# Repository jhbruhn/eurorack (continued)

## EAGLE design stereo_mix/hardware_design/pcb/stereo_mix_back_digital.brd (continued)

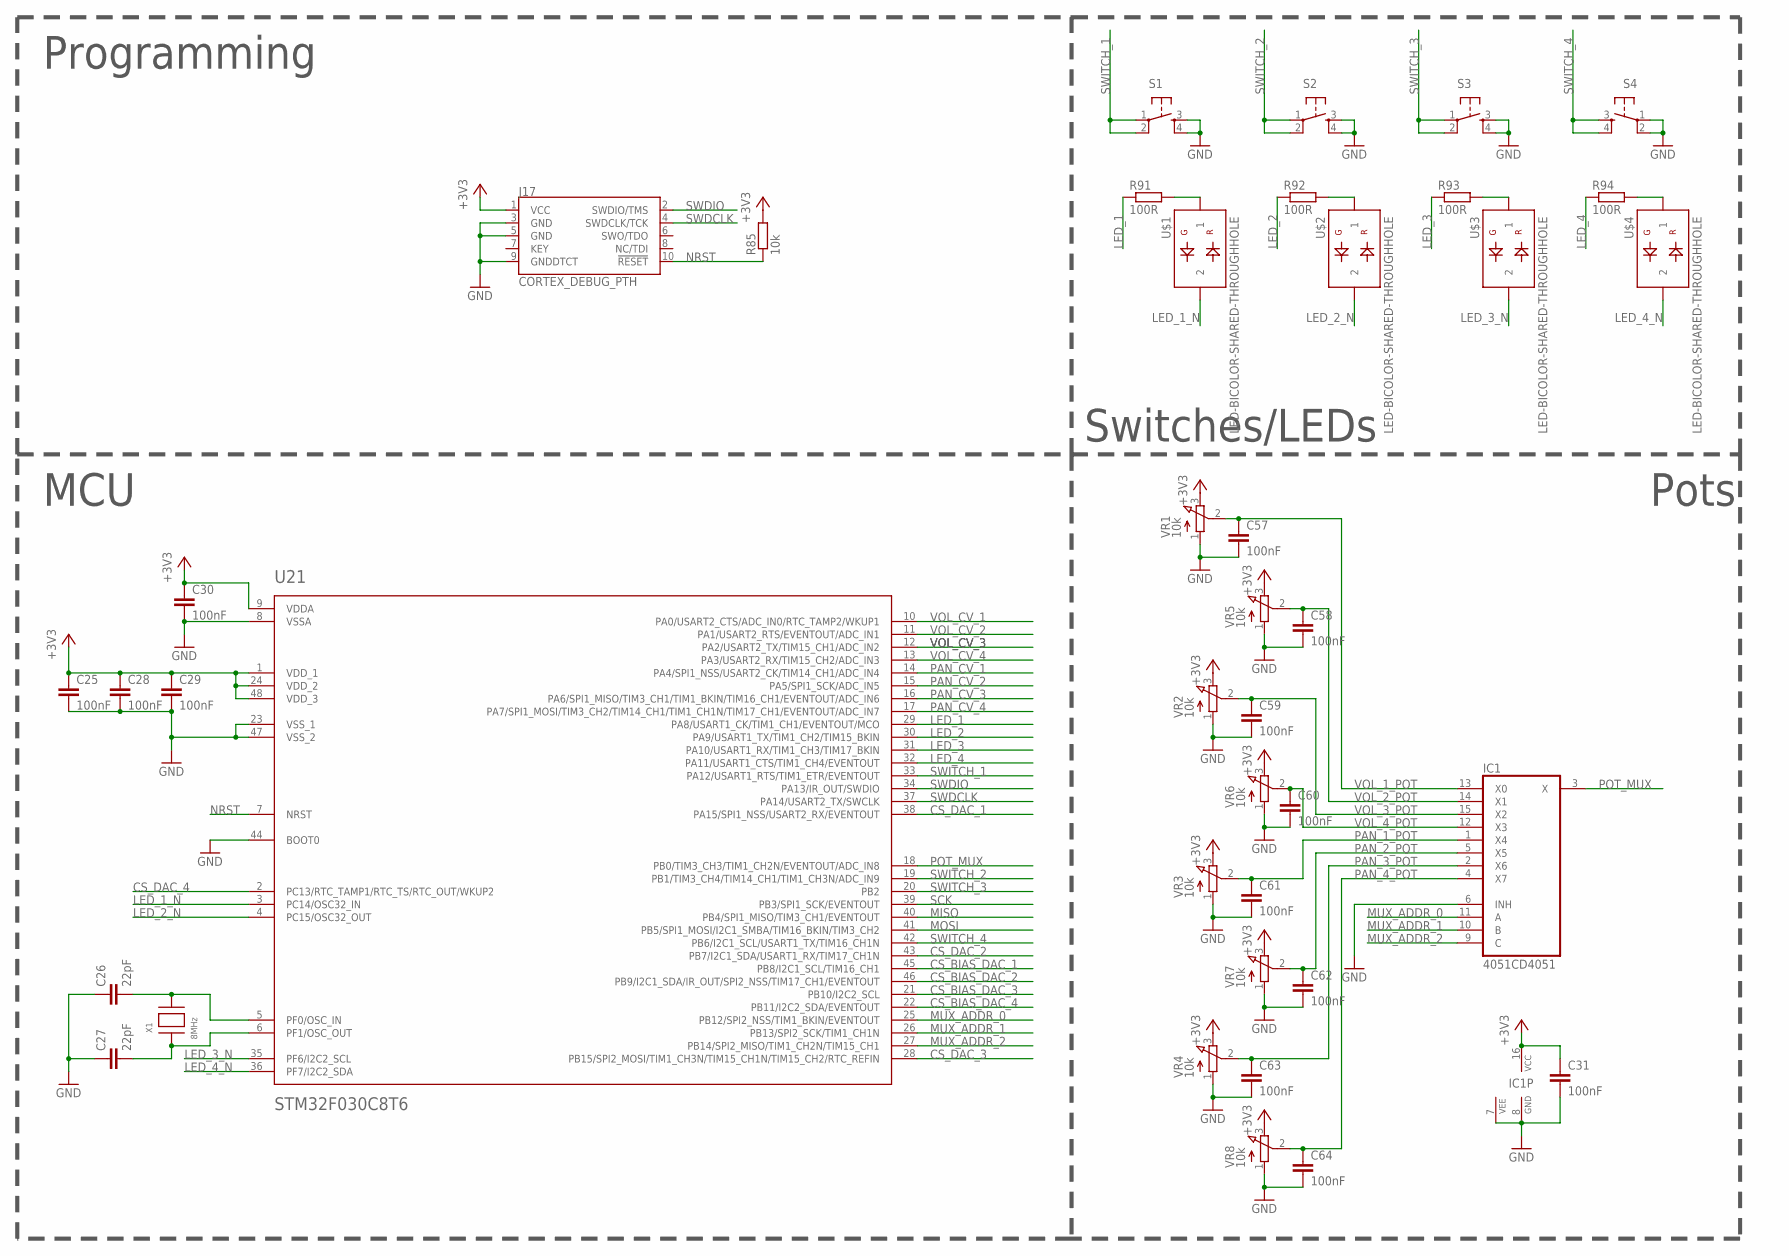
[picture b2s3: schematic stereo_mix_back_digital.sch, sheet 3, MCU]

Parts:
C25, C28, C29, C30, C31, C57, C58, C59, C60, C61, C62, C63, C64: 100nF; C0402
C26, C27: 22pF; C0402
IC1: 4051CD4051; SOIC16N
J17: CORTEX_DEBUG_PTH; 2X5-PTH-1.27MM
R85: 10k; R0402
R91, R92, R93, R94: 100R; R0402
S1, S2, S3, S4: TAC_SWITCHPTH; TACTILE-PTH
U21: STM32F030C8T6; LQFP48
U$1, U$2, U$3, U$4: LED-BICOLOR-SHARED-THROUGHHOLE; LED3MM
VR1, VR2, VR3, VR4, VR5, VR6, VR7, VR8: 10k; 9MM_SNAP-IN_POT
X1: 8MHz; NX5032

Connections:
+3V3: C25.1, C28.1, C29.1, C30.1, C31.1, IC1.16 (VCC), J17.1 (VCC), R85.2, U21.1 (VDD_1), U21.9 (VDDA), U21.24 (VDD_2), U21.48 (VDD_3), VR1.3 (E), VR2.3 (E), VR3.3 (E), VR4.3 (E), VR5.3 (E), VR6.3 (E), VR7.3 (E), VR8.3 (E); also elsewhere on the board
CS_BIAS_DAC_1: U21.45 (PB8/I2C1_SCL/TIM16_CH1); also elsewhere on the board
CS_BIAS_DAC_2: U21.46 (PB9/I2C1_SDA/IR_OUT/SPI2_NSS/TIM17_CH1/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); also elsewhere on the board
CS_BIAS_DAC_3: U21.21 (PB10/I2C2_SCL); also elsewhere on the board
CS_BIAS_DAC_4: U21.22 (PB11/I2C2_SDA/EVENTOUT); also elsewhere on the board
CS_DAC_1: U21.38 (PA15/SPI1_NSS/USART2_RX/EVENTOUT); also elsewhere on the board
CS_DAC_2: U21.43 (PB7/I2C1_SDA/USART1_RX/TIM17_CH1N); also elsewhere on the board
CS_DAC_3: U21.28 (PB15/SPI2_MOSI/TIM1_CH3N/TIM15_CH1N/TIM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); also elsewhere on the board
CS_DAC_4: U21.2 (PC13/RTC_TAMP1/RTC_TS/RTC_OUT/WKUP2); also elsewhere on the board
GND: C25.2, C26.1, C27.1, C28.2, C29.2, C30.2, C31.2, C57.2, C58.2, C59.2, C60.2, C61.2, C62.2, C63.2, C64.2, IC1.6 (INH), IC1.7 (VEE), IC1.8 (GND), J17.3 (GND), J17.5 (GND), J17.9 (GNDDTCT), S1.3, S1.4, S2.3, S2.4, S3.3, S3.4, S4.1, S4.2, U21.8 (VSSA), U21.23 (VSS_1), U21.44 (BOOT0), U21.47 (VSS_2), VR1.1 (A), VR2.1 (A), VR3.1 (A), VR4.1 (A), VR5.1 (A), VR6.1 (A), VR7.1 (A), VR8.1 (A); also elsewhere on the board
LED_1: R91.1, U21.29 (PA8/USART1_CK/TIM1_CH1/EVENTOUT/MCO)
LED_1_N: U21.3 (PC14/OSC32_IN), U$1.2
LED_2: R92.1, U21.30 (PA9/USART1_TX/TIM1_CH2/TIM15_BKIN)
LED_2_N: U21.4 (PC15/OSC32_OUT), U$2.2
LED_3: R93.1, U21.31 (PA10/USART1_RX/TIM1_CH3/TIM17_BKIN)
LED_3_N: U21.35 (PF6/I2C2_SCL), U$3.2
LED_4: R94.1, U21.32 (PA11/USART1_CTS/TIM1_CH4/EVENTOUT)
LED_4_N: U21.36 (PF7/I2C2_SDA), U$4.2
MISO: U21.40 (PB4/SPI1_MISO/TIM3_CH1/EVENTOUT)
MOSI: U21.41 (PB5/SPI1_MOSI/I2C1_SMBA/TIM16_BKIN/TIM3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); also elsewhere on the board
MUX_ADDR_0: IC1.11 (A), U21.25 (PB12/SPI2_NSS/TIM1_BKIN/EVENTOUT)
MUX_ADDR_1: IC1.10 (B), U21.26 (PB13/SPI2_SCK/TIM1_CH1N)
MUX_ADDR_2: IC1.9 (C), U21.27 (PB14/SPI2_MISO/TIM1_CH2N/TIM15_CH1)
unnamed: R91.2, U$1.1
unnamed: R92.2, U$2.1
unnamed: R93.2, U$3.1
unnamed: R94.2, U$4.1
unnamed: C27.2, U21.6 (PF1/OSC_OUT), X1.P$1
unnamed: C26.2, U21.5 (PF0/OSC_IN), X1.P$2
NRST: J17.10 (!RESET), R85.1, U21.7 (NRST)
PAN_1_POT: C61.1, IC1.1 (X4), VR3.2 (S)
PAN_2_POT: C62.1, IC1.5 (X5), VR7.2 (S)
PAN_3_POT: C63.1, IC1.2 (X6), VR4.2 (S)
PAN_4_POT: C64.1, IC1.4 (X7), VR8.2 (S)
PAN_CV_1: U21.14 (PA4/SPI1_NSS/USART2_CK/TIM14_CH1/ADC_IN4); also elsewhere on the board
PAN_CV_2: U21.15 (PA5/SPI1_SCK/ADC_IN5); also elsewhere on the board
PAN_CV_3: U21.16 (PA6/SPI1_MISO/TIM3_CH1/TIM1_BKIN/TIM16_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); also elsewhere on the board
PAN_CV_4: U21.17 (PA7/SPI1_MOSI/TIM3_CH2/TIM14_CH1/TIM1_C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); also elsewhere on the board
POT_MUX: IC1.3 (X), U21.18 (PB0/TIM3_CH3/TIM1_CH2N/EVENTOUT/ADC_IN8)
SCK: U21.39 (PB3/SPI1_SCK/EVENTOUT); also elsewhere on the board
SWDCLK: J17.4 (SWDCLK/TCK), U21.37 (PA14/USART2_TX/SWCLK)
SWDIO: J17.2 (SWDIO/TMS), U21.34 (PA13/IR_OUT/SWDIO)
SWITCH_1: S1.1, S1.2, U21.33 (PA12/USART1_RTS/TIM1_ETR/EVENTOUT)
SWITCH_2: S2.1, S2.2, U21.19 (PB1/TIM3_CH4/TIM14_CH1/TIM1_CH3N/ADC_IN9)
SWITCH_3: S3.1, S3.2, U21.20 (PB2)
SWITCH_4: S4.3, S4.4, U21.42 (PB6/I2C1_SCL/USART1_TX/TIM16_CH1N)
VOL_1_POT: C57.1, IC1.13 (X0), VR1.2 (S)
VOL_2_POT: C58.1, IC1.14 (X1), VR5.2 (S)
VOL_3_POT: C59.1, IC1.15 (X2), VR2.2 (S)
VOL_4_POT: C60.1, IC1.12 (X3), VR6.2 (S)
VOL_CV_1: U21.10 (PA0/USART2_CTS/ADC_IN0/RTC_TAMP2/WKUP1); also elsewhere on the board
VOL_CV_2: U21.11 (PA1/USART2_RTS/EVENTOUT/ADC_IN1); also elsewhere on the board
VOL_CV_3: U21.12 (PA2/USART2_TX/TIM15_CH1/ADC_IN2); also elsewhere on the board
VOL_CV_4: U21.13 (PA3/USART2_RX/TIM15_CH2/ADC_IN3); also elsewhere on the board

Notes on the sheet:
MCU
Pots
Switches/LEDs
Programming

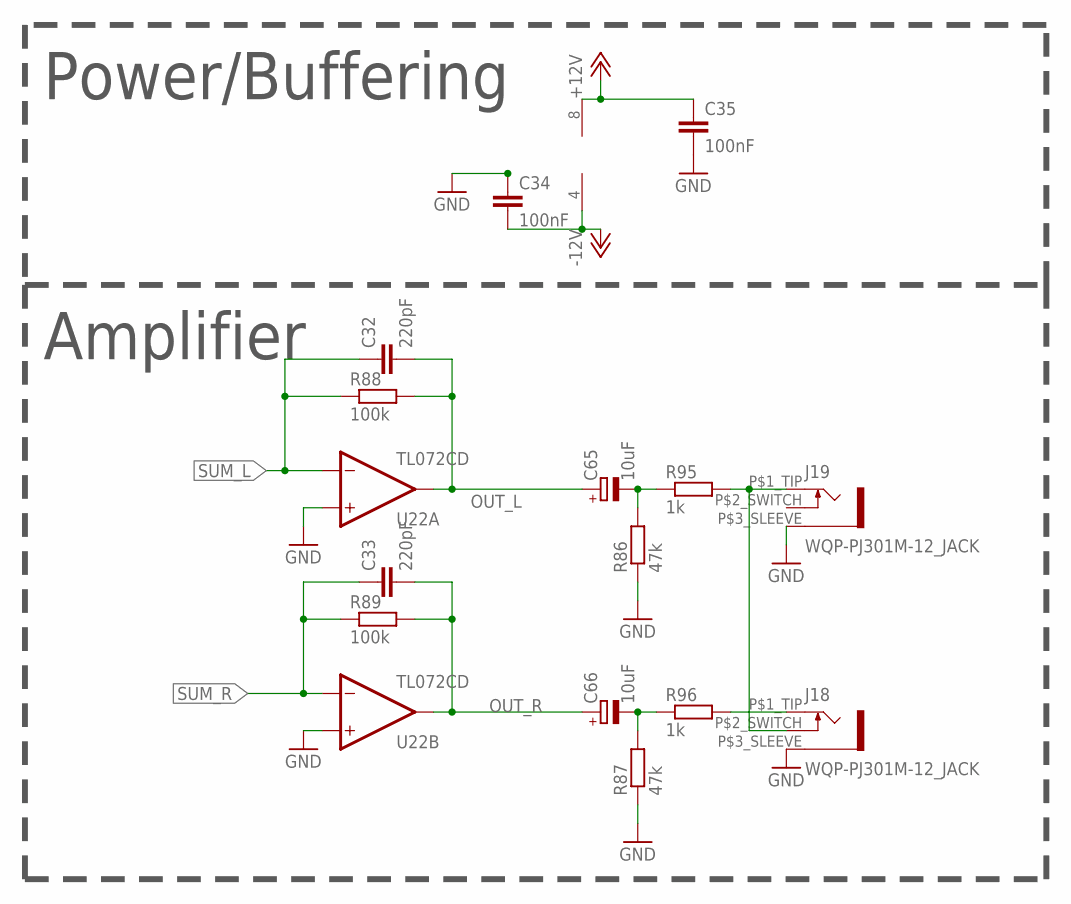
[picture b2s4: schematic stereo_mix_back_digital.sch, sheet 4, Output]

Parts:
C32, C33: 220pF; C0402
C34, C35: 100nF; C0402
C65, C66: 10uF; CASE-A_3216
J18, J19: WQP-PJ301M-12_JACK
R86, R87: 47k; R0402
R88, R89: 100k; R0402
R95, R96: 1k; R0402
U22: TL072CD; SOIC8

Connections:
+12V: C35.1, U22.8 (V+); also elsewhere on the board
-12V: C34.2, U22.4 (V-); also elsewhere on the board
GND: C34.1, C35.2, J18.P$3_SLEEVE (1), J19.P$3_SLEEVE (1), R86.1, R87.1, U22.3 (+IN), U22.5 (+IN); also elsewhere on the board
unnamed: J18.P$2_SWITCH (3), J19.P$1_TIP (2), R95.2
unnamed: C65.-, R86.2, R95.1
unnamed: J18.P$1_TIP (2), R96.2
unnamed: C66.-, R87.2, R96.1
OUT_L: C32.2, C65.+, R88.2, U22.1 (OUT)
OUT_R: C33.2, C66.+, R89.2, U22.7 (OUT)
SUM_L: C32.1, R88.1, U22.2 (-IN); also elsewhere on the board
SUM_R: C33.1, R89.1, U22.6 (-IN); also elsewhere on the board

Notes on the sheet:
Power/Buffering
Amplifier

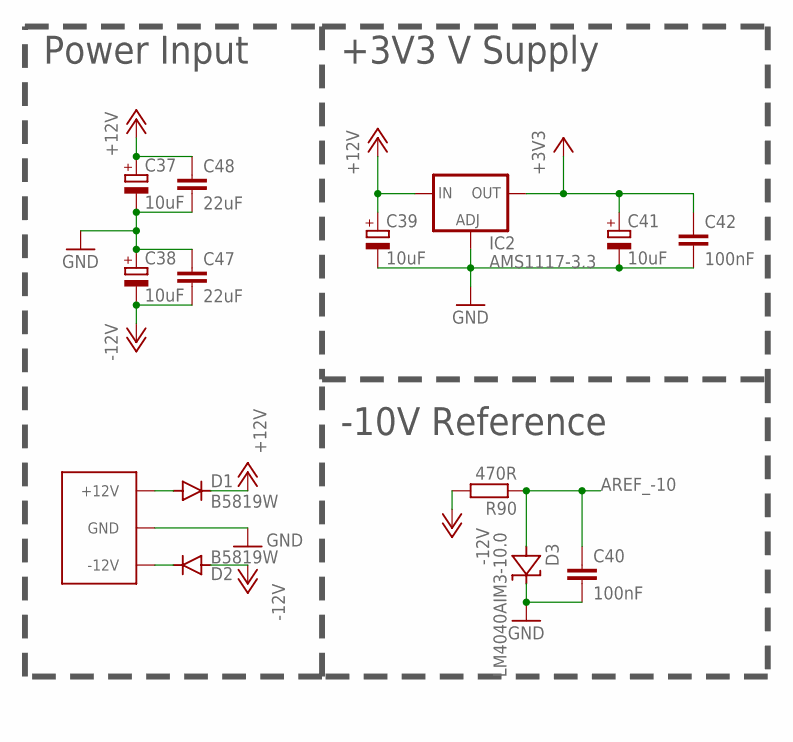
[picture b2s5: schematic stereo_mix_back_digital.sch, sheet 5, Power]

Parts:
C36: EURO_POWER_LOCKFAT-LOCK; EURO_PWR_HEADER_LOCK
C37, C38, C39, C41: 10uF; CASE-A_3216
C40, C42: 100nF; C0402
C47, C48: 22uF; C0805
D1, D2: B5819W; SOD123
D3: LM4040AIM3-10.0; SOT23
IC2: AMS1117-3.3; SOT223
R90: 470R; R0402

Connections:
+3V3: C41.+, C42.1, IC2.4 (OUT); also elsewhere on the board
+12V: C37.+, C39.+, C48.1, D1.C, IC2.3 (IN); also elsewhere on the board
-12V: C38.-, C47.2, D2.A, R90.2; also elsewhere on the board
AREF_-10: C40.1, D3.2 (A), R90.1; also elsewhere on the board
GND: C36.GND1 (GND), C36.GND2 (GND), C36.GND3 (GND), C36.GND4 (GND), C36.GND5 (GND), C36.GND6 (GND), C37.-, C38.+, C39.-, C40.2, C41.-, C42.2, C47.1, C48.2, D3.1 (C), IC2.1 (ADJ); also elsewhere on the board
unnamed: C36.POS1 (+12V), C36.POS2 (+12V), D1.A
unnamed: C36.NEG1 (-12V), C36.NEG2 (-12V), D2.C

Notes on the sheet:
Power Input
+3V3 V Supply
-10V Reference

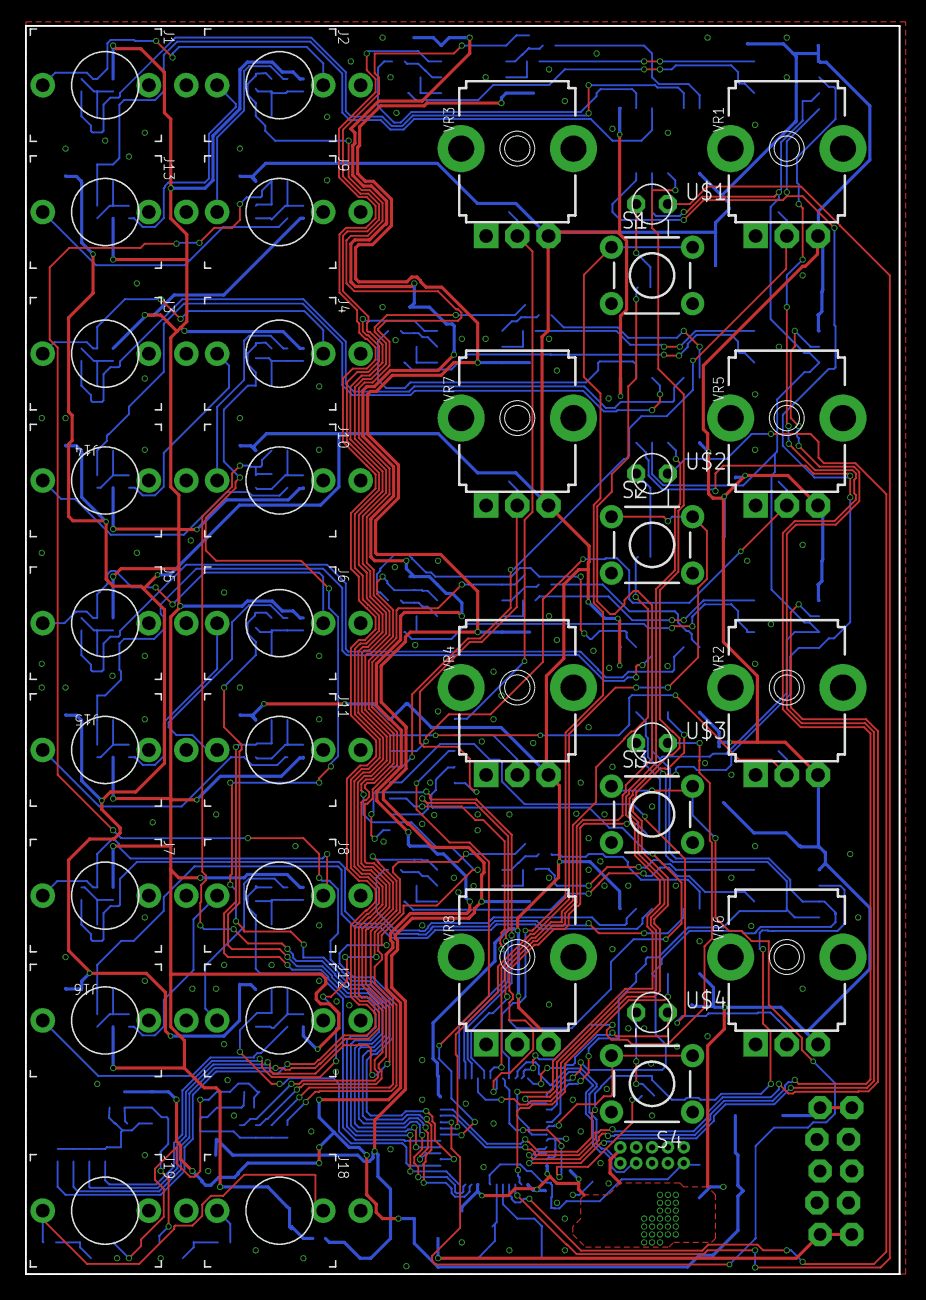
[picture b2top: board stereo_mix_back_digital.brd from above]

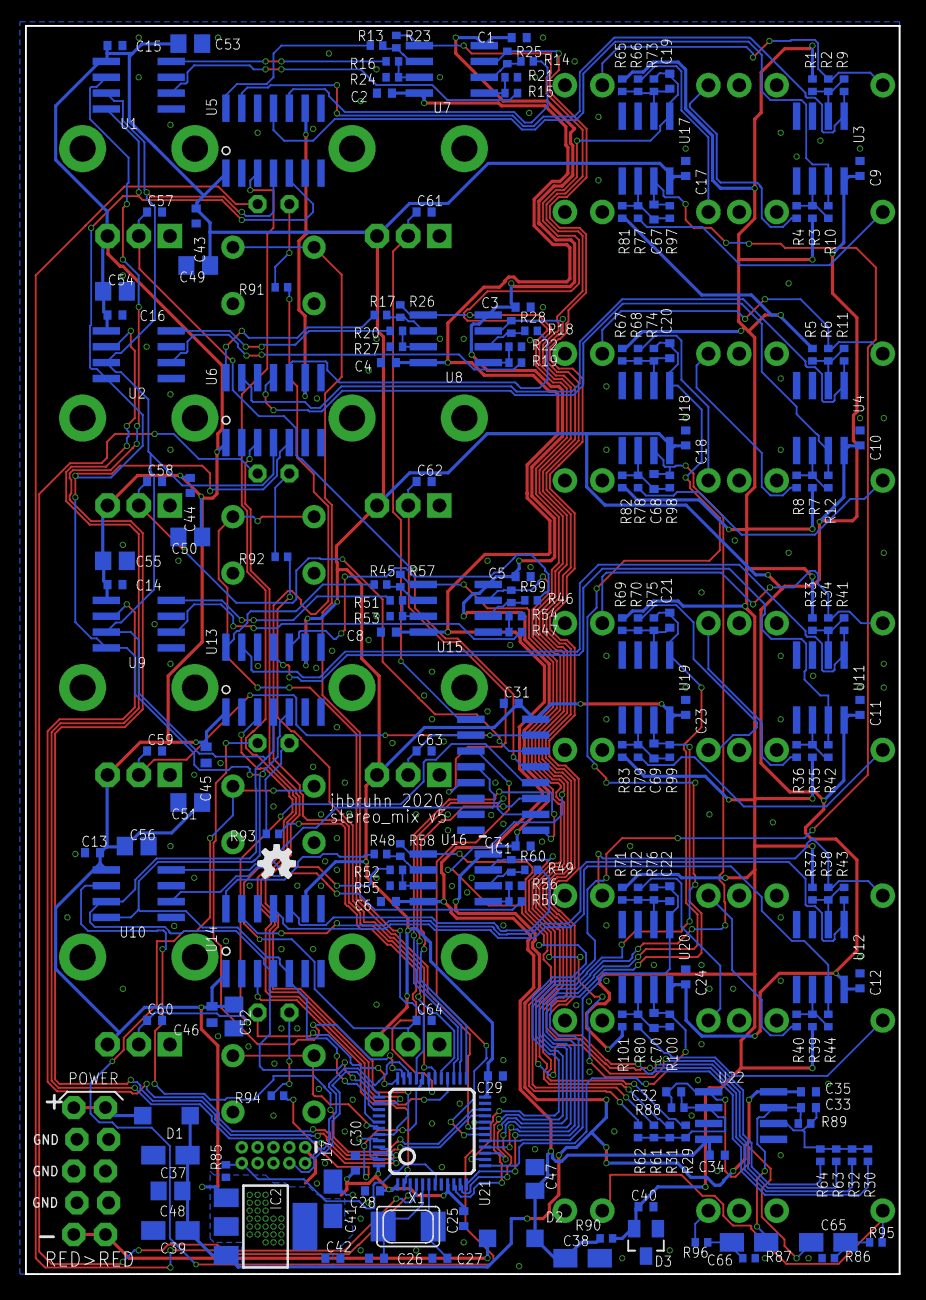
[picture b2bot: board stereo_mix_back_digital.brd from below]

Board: 2 copper layers, 70.0 x 100.0 mm, 234 parts (200 on the bottom side), 146 nets.

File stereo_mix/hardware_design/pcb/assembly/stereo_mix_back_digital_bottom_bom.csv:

Comment,Designator,Footprint,LCSC Part #
1.0nF,C19 C20 C21 C22 C67 C68 C69 C70,C0402,
1k,R95 R96,R0402,
8MHz,X1,NX5032,
10k,R85,R0402,
10uF,C37 C38 C39 C41,CASE-A_3216,
10uF,C49 C50 C51 C52 C53 C54 C55 C56,C0805,
10uF,C65 C66,CASE-A_3216,
15k,R9 R10 R11 R12 R41 R42 R43 R44,R0402,
20k,R73 R74 R75 R76 R97 R98 R99 R100,R0402,
22pF,C26 C27,C0402,
22uF,C47 C48,C0805,
47k,R13 R14 R15 R16 R17 R18 R19 R20 R45 R46 R47 R48 R49 R50 R51 R52 R86 R87,R0402,
91k,R1 R3 R5 R7 R33 R35 R37 R39,R0402,
100R,R91 R92 R93 R94,R0402,
100k,R2 R4 R6 R8 R21 R22 R24 R27 R29 R30 R31 R32 R34 R36 R38 R40 R53 R54 R55 R56 R61 R62 R63 R64 R66 R68 R70 R72 R88 R89,R0402,
100nF,C1 C2 C3 C4 C5 C6 C7 C8 C9 C10 C11 C12 C13 C14 C15 C16 C17 C18 C23 C24 C25 C28 C29 C30 C31 C34 C35 C40 C42 C43 C44 C45 C46 C57 C58 C59 C60 C61 C62 C63 C64,C0402,
120k,R65 R67 R69 R71 R81 R82 R83 R101,R0402,
200k,R77 R78 R79 R80,R0402,
220pF,C32 C33,C0402,
300k,R23 R25 R26 R28 R57 R58 R59 R60,R0402,
470R,R90,R0402,
4051CD4051,IC1,SOIC16N,
AMS1117-3.3,IC2,SOT223,
B5819W,D1 D2,SOD123,
LM4040AIM3-10.0,D3,SOT23,
MCP4822E-SN,U1 U2 U9 U10,SOIC8,
MCP4922E/SL,U5 U6 U13 U14,SO-14,
MCP6002T-I/SN,U3 U4 U11 U12 U17 U18 U19 U20,SOIC8,
STM32F030C8T6,U21,LQFP48,
TL072CD,U7 U8 U15 U16 U22,SOIC8,

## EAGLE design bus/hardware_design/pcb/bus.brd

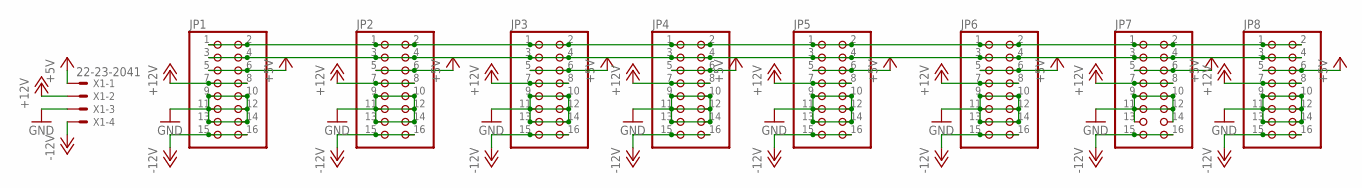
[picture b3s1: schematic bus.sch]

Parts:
JP1, JP2, JP3, JP4, JP5, JP6, JP7, JP8: PINHD-2X8; 2X08
X1: 22-23-2041

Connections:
+5V: JP1.5, JP1.6, JP2.5, JP2.6, JP3.5, JP3.6, JP4.5, JP4.6, JP5.5, JP5.6, JP6.5, JP6.6, JP7.5, JP7.6, JP8.5, JP8.6, X1.1
+12V: JP1.7, JP1.8, JP2.7, JP2.8, JP3.7, JP3.8, JP4.7, JP4.8, JP5.7, JP5.8, JP6.7, JP6.8, JP7.7, JP7.8, JP8.7, JP8.8, X1.2
-12V: JP1.15, JP1.16, JP2.15, JP2.16, JP3.15, JP3.16, JP4.15, JP4.16, JP5.15, JP5.16, JP6.15, JP6.16, JP7.15, JP7.16, JP8.15, JP8.16, X1.4
GND: JP1.9, JP1.10, JP1.11, JP1.12, JP1.13, JP1.14, JP2.9, JP2.10, JP2.11, JP2.12, JP2.13, JP2.14, JP3.9, JP3.10, JP3.11, JP3.12, JP3.13, JP3.14, JP4.9, JP4.10, JP4.11, JP4.12, JP4.13, JP4.14, JP5.9, JP5.10, JP5.11, JP5.12, JP5.13, JP5.14, JP6.9, JP6.10, JP6.11, JP6.12, JP6.13, JP6.14, JP7.9, JP7.10, JP7.11, JP7.12, JP7.13, JP7.14, JP8.9, JP8.10, JP8.11, JP8.12, JP8.13, JP8.14, X1.3
unnamed: JP1.3, JP1.4, JP2.3, JP2.4, JP3.3, JP3.4, JP4.3, JP4.4, JP5.3, JP5.4, JP6.3, JP6.4, JP7.3, JP7.4, JP8.3, JP8.4
unnamed: JP1.1, JP1.2, JP2.1, JP2.2, JP3.1, JP3.2, JP4.1, JP4.2, JP5.1, JP5.2, JP6.1, JP6.2, JP7.1, JP7.2, JP8.1, JP8.2

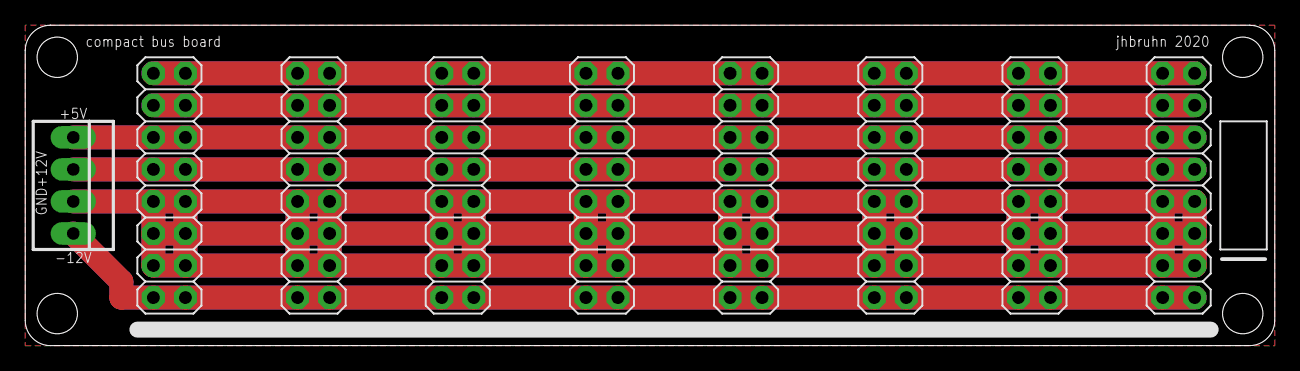
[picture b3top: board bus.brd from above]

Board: 2 copper layers, 99.1 x 25.4 mm, 9 parts (0 on the bottom side), 6 nets.

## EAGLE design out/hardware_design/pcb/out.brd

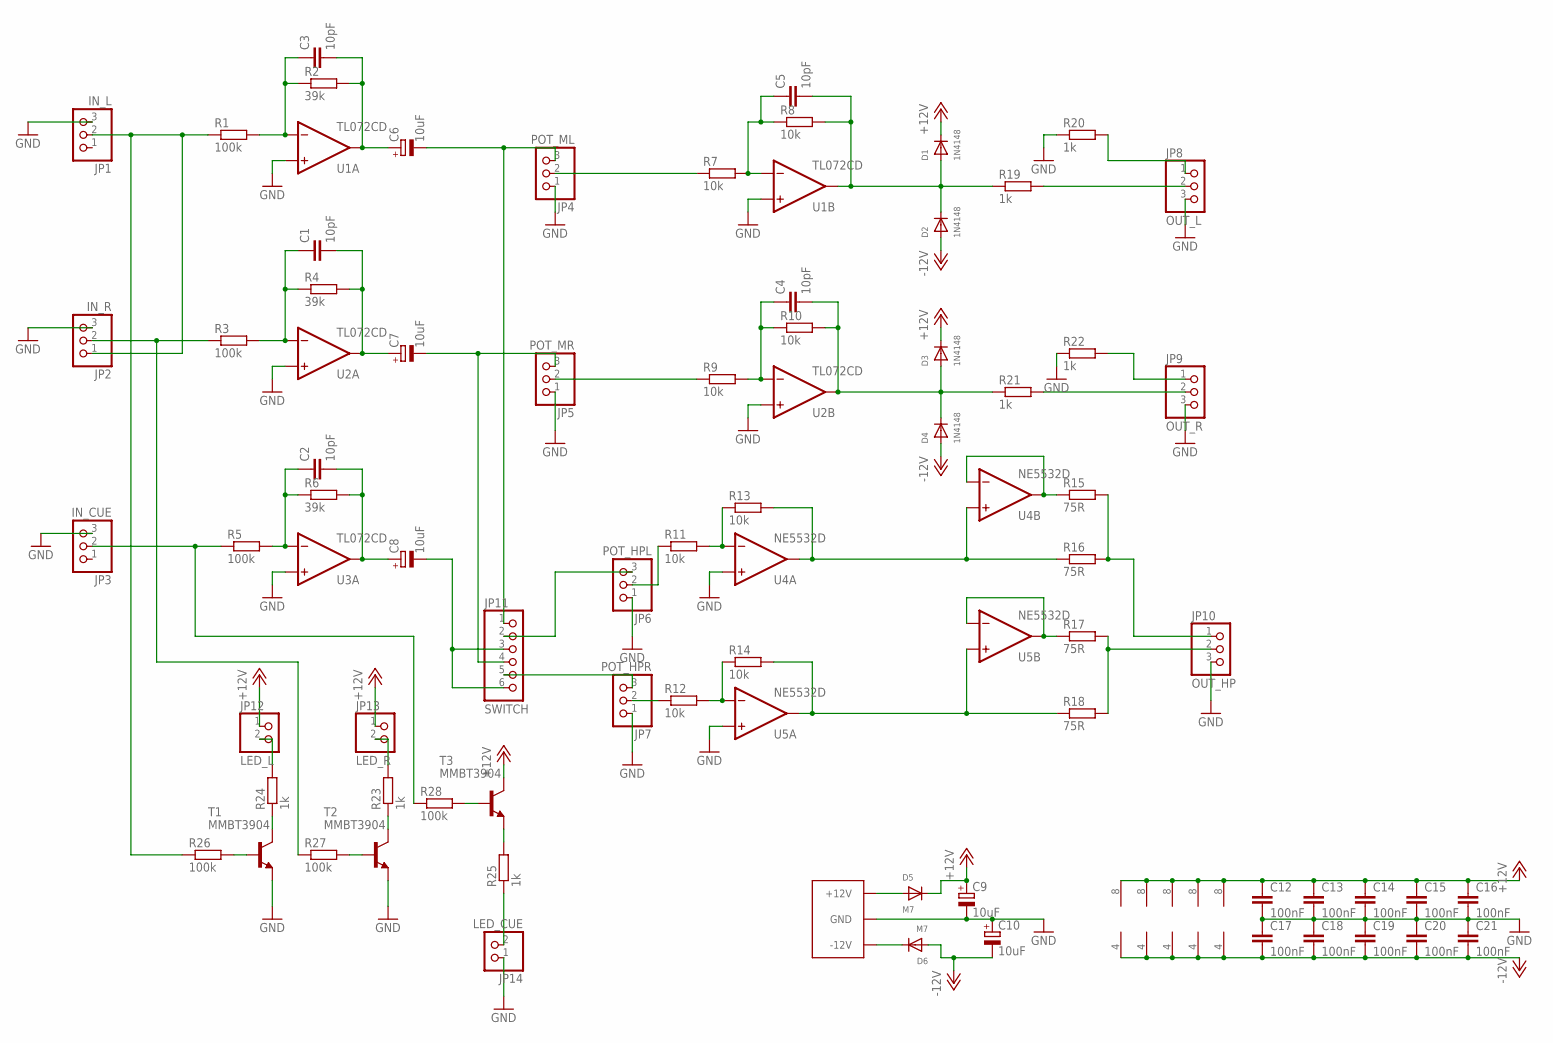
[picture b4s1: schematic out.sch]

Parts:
C1, C2, C3, C4, C5: 10pF; C0402
C6, C7, C8, C9, C10: 10uF; A/3216-18W
C11: EURO_POWER_LOCKFAT-LOCK; EURO_PWR_HEADER_LOCK
C12, C13, C14, C15, C16, C17, C18, C19, C20, C21: 100nF; C0402
D1, D2, D3, D4: 1N4148; SOD-323F
D5, D6: M7; SMADIODE
JP1: IN_L; 1X03
JP2: IN_R; 1X03
JP3: IN_CUE; 1X03
JP4: POT_ML; 1X03
JP5: POT_MR; 1X03
JP6: POT_HPL; 1X03
JP7: POT_HPR; 1X03
JP8: OUT_L; 1X03
JP9: OUT_R; 1X03
JP10: OUT_HP; 1X03
JP11: SWITCH; 1X06
JP12: LED_L; 1X02
JP13: LED_R; 1X02
JP14: LED_CUE; 1X02
R1, R3, R5, R26, R27, R28: 100k; R0402
R2, R4, R6: 39k; R0402
R7, R8, R9, R10, R11, R12, R13, R14: 10k; R0402
R15, R16, R17, R18: 75R; R0402
R19, R20, R21, R22, R23, R24, R25: 1k; R0402
T1, T2, T3: MMBT3904; SOT23-BEC
U1, U2, U3: TL072CD; SOIC8
U4, U5: NE5532D; SOIC8

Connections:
+12V: C9.+, C12.1, C13.1, C14.1, C15.1, C16.1, D1.C, D3.C, D5.C, JP12.1, JP13.1, T3.C, U1.8 (V+), U2.8 (V+), U3.8 (V+), U4.8 (V+), U5.8 (V+)
-12V: C10.-, C17.2, C18.2, C19.2, C20.2, C21.2, D2.A, D4.A, D6.A, U1.4 (V-), U2.4 (V-), U3.4 (V-), U4.4 (V-), U5.4 (V-)
GND: C9.-, C10.+, C11.GND1 (GND), C11.GND2 (GND), C11.GND3 (GND), C11.GND4 (GND), C11.GND5 (GND), C11.GND6 (GND), C12.2, C13.2, C14.2, C15.2, C16.2, C17.1, C18.1, C19.1, C20.1, C21.1, JP1.3, JP2.3, JP3.3, JP4.1, JP5.1, JP6.1, JP7.1, JP8.3, JP9.3, JP10.3, JP14.1, R20.1, R22.1, T1.E, T2.E, U1.3 (+IN), U1.5 (+IN), U2.3 (+IN), U2.5 (+IN), U3.3 (+IN), U4.3 (+IN), U5.3 (+IN)
unnamed: C5.2, D1.A, D2.C, R8.2, R19.1, U1.7 (OUT)
unnamed: C4.2, D3.A, D4.C, R10.2, R21.1, U2.7 (OUT)
unnamed: C5.1, R7.2, R8.1, U1.6 (-IN)
unnamed: R15.1, U4.6 (-IN), U4.7 (OUT)
unnamed: JP10.1, R15.2, R16.2
unnamed: R14.2, R18.1, U5.1 (OUT), U5.5 (+IN)
unnamed: R17.1, U5.6 (-IN), U5.7 (OUT)
unnamed: C4.1, R9.2, R10.1, U2.6 (-IN)
unnamed: JP10.2, R17.2, R18.2
unnamed: JP4.2, R7.1
unnamed: R11.2, R13.1, U4.2 (-IN)
unnamed: R13.2, R16.1, U4.1 (OUT), U4.5 (+IN)
unnamed: R12.2, R14.1, U5.2 (-IN)
unnamed: C2.1, R5.2, R6.1, U3.2 (-IN)
unnamed: C6.-, JP4.3, JP11.1
unnamed: C2.2, C8.+, R6.2, U3.1 (OUT)
unnamed: C7.-, JP5.3, JP11.4
unnamed: JP5.2, R9.1
unnamed: C1.1, R3.2, R4.1, U2.2 (-IN)
unnamed: JP7.2, R12.1
unnamed: C1.2, C7.+, R4.2, U2.1 (OUT)
unnamed: JP6.2, R11.1
unnamed: JP8.2, R19.2
unnamed: C3.1, R1.2, R2.1, U1.2 (-IN)
unnamed: JP9.2, R21.2
unnamed: C3.2, C6.+, R2.2, U1.1 (OUT)
unnamed: JP9.1, R22.2
unnamed: JP8.1, R20.2
unnamed: JP1.2, JP2.1, R1.1, R26.1
unnamed: C11.POS1 (+12V), C11.POS2 (+12V), D5.A
unnamed: JP3.2, R5.1, R28.1
unnamed: JP6.3, JP11.2
unnamed: C8.-, JP11.3, JP11.6
unnamed: JP7.3, JP11.5
unnamed: R24.1, T1.C
unnamed: R26.2, T1.B
unnamed: R23.1, T2.C
unnamed: R28.2, T3.B
unnamed: R25.2, T3.E
unnamed: JP14.2, R25.1
unnamed: JP13.2, R23.2
unnamed: JP12.2, R24.2
unnamed: C11.NEG1 (-12V), C11.NEG2 (-12V), D6.C
unnamed: R27.2, T2.B
unnamed: JP2.2, R3.1, R27.1

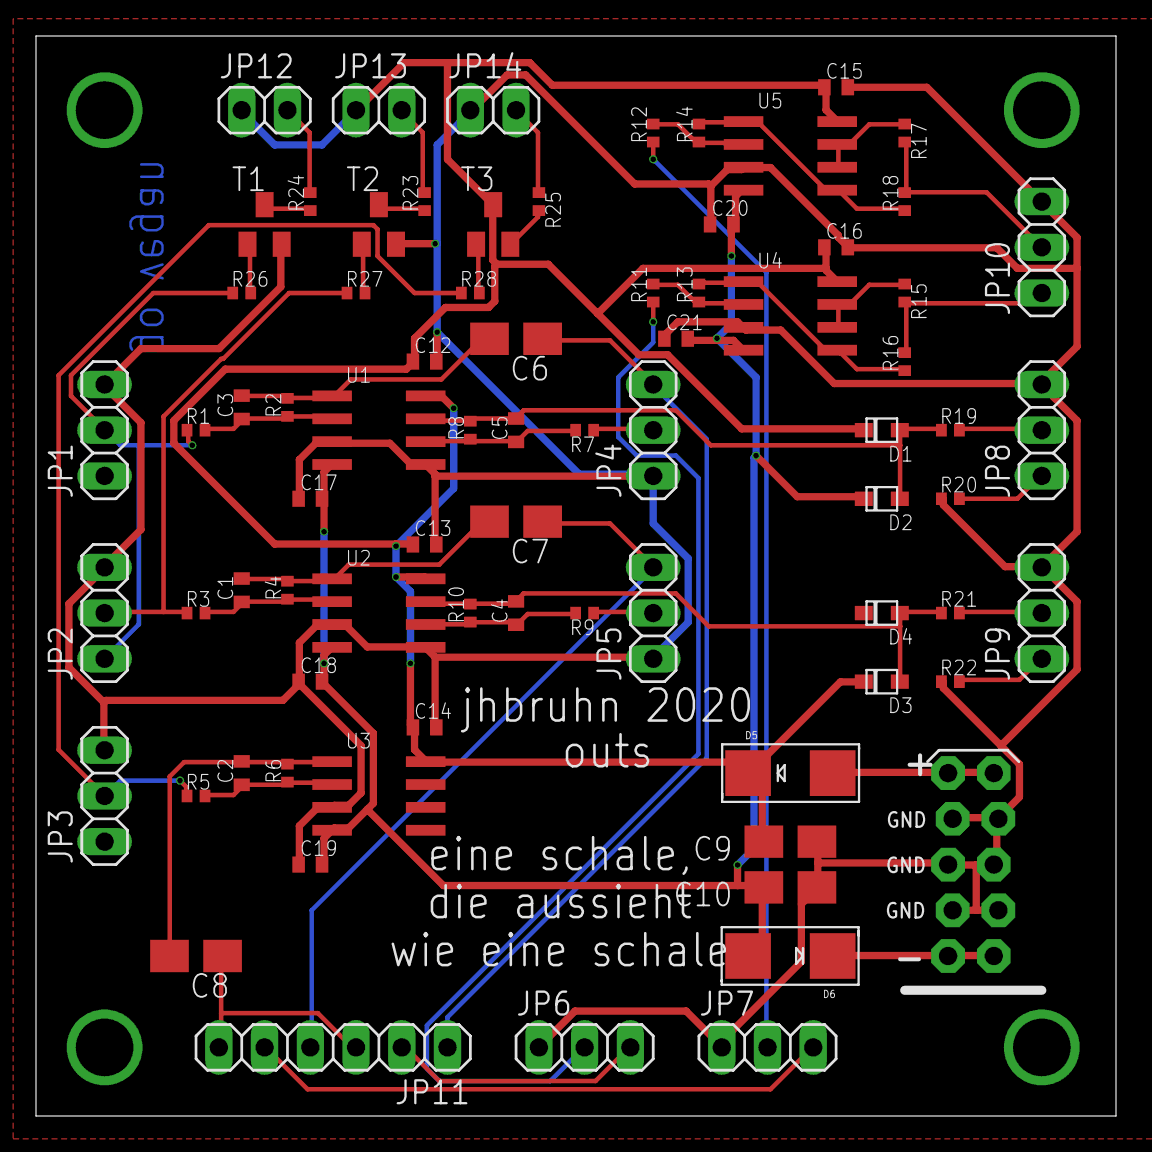
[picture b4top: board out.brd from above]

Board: 2 copper layers, 60.0 x 60.0 mm, 77 parts (0 on the bottom side), 48 nets.

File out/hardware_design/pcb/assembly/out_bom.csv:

"Comment","Designator","Footprint","LCSC Part #","LCSC Part Type"
"100k","R1, R3, R5, R26, R27, R28","0402_R","",""
"100nF","C12, C13, C14, C15, C16, C17, C18, C19, C20, C21","0402_C","",""
"10k","R7, R8, R9, R10, R11, R12, R13, R14","0402_R","",""
"10pF","C1, C2, C3, C4, C5","0402_C","",""
"10uF","C6, C7, C8, C9, C10","A/3216-18W","",""
"1N4148","D1, D2, D3, D4","SOD-323F","",""
"1k","R19, R20, R21, R22, R23, R24, R25","0402_R","",""
"39k","R2, R4, R6","0402_R","",""
"75R","R15, R16, R17, R18","0402_R","",""
"EURO_POWER_LOCKFAT-LOCK","C11","EURO_PWR_HEADER_LOCK","",""
"IN_CUE","JP3","1X03","",""
"IN_L","JP1","1X03","",""
"IN_R","JP2","1X03","",""
"LED_CUE","JP14","1X02","",""
"LED_L","JP12","1X02","",""
"LED_R","JP13","1X02","",""
"M7","D5, D6","SMADIODE","",""
"MMBT3904","T1, T2, T3","SOT23-BEC","",""
"NE5532D","U4, U5","SOIC8","",""
"OUT_HP","JP10","1X03","",""
"OUT_L","JP8","1X03","",""
"OUT_R","JP9","1X03","",""
"POT_HPL","JP6","1X03","",""
"POT_HPR","JP7","1X03","",""
"POT_ML","JP4","1X03","",""
"POT_MR","JP5","1X03","",""
"SWITCH","JP11","1X06","",""
"TL072CD","U1, U2, U3","SOIC8","",""

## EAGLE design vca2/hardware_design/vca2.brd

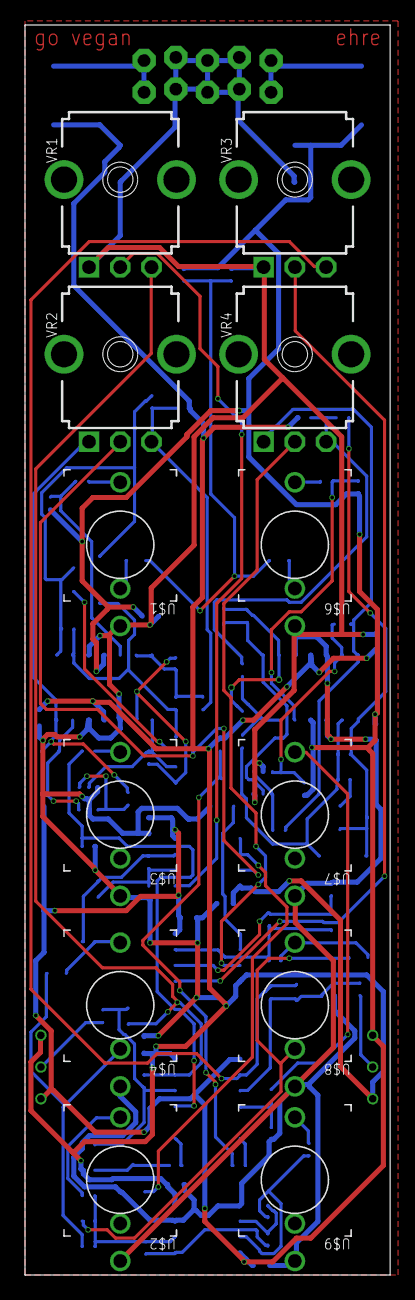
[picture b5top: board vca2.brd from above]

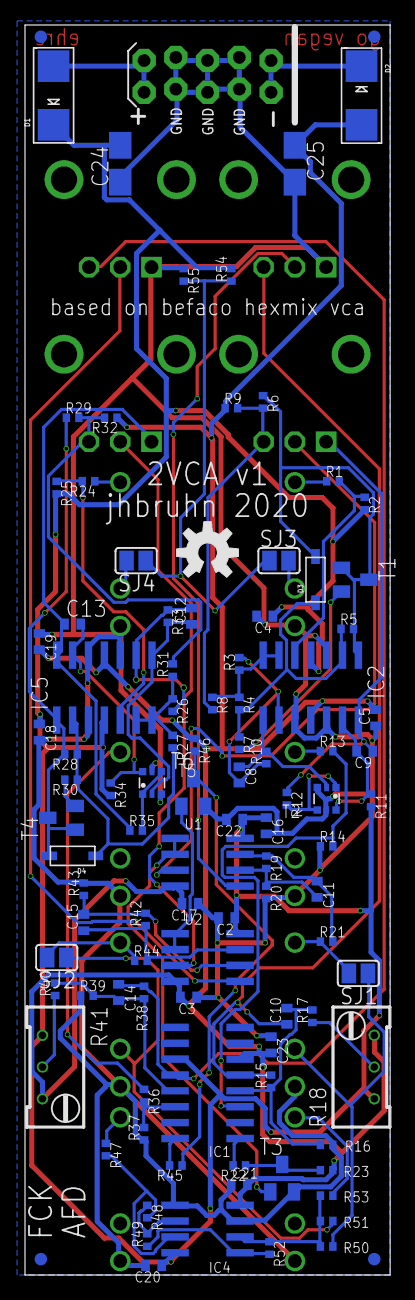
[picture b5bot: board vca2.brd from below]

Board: 2 copper layers, 29.2 x 100.0 mm, 115 parts (103 on the bottom side), 66 nets.

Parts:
C1: EURO_POWER_LOCKFAT-LOCK; EURO_PWR_HEADER_LOCK
C2, C3, C4, C5, C16, C17, C18, C19, C20, C21, C22, C23: 100nF; C0402
C8, C9, C12, C13: 100pF; C0402
C10, C11, C14, C15: 22pF; C0402
C24, C25: 10uF; A/3216-18W
D1, D2: STTH102A; SMADIODE
D3, D4: 1N4148-2; SOD-123
FD1, FD2, FD3, FD4: FIDUCIAL1X2; FIDUCIAL-1X2
IC1: LM13700M; SO16
IC2, IC5: NCS20074D; SO14
IC4: TL072CD; SOIC8
LOGO1: OSHW-LOGOM; OSHW-LOGO-M
R1, R21, R24, R44, R47: 1k; R0402
R2, R3, R17, R25, R26, R40: 1M; R0402
R4, R5, R13, R19, R27, R28, R36, R42, R48, R49, R50, R51, R52, R53: 100k; R0402
R6, R7, R29, R30: 220R; R0402
R8, R31: 56k; R0402
R9, R32: 33k; R0402
R10, R33, R54: 10k; R0402
R11, R34: 10M; R0402
R12, R35: 1k5; R0402
R14, R16, R37, R39: 680R; R0402
R15, R38: 47k; R0402
R18, R41: 100k; RTRIM64W
R20, R43: 68k; R0402
R22, R45: 15k; R0402
R23, R46: 680k; R0402
R55: 50k; R0402
SJ1, SJ2, SJ3, SJ4: SJ
T1, T3, T4, T6: 2N3906; SOT23-BEC
T2, T5: BC847BS; SOT363
U1, U2: TL072CD; SOIC8
U$1, U$2, U$3, U$4, U$6, U$7, U$8, U$9: WQP-PJ301M-12_JACK
VR1, VR2, VR3, VR4: 100k; 9MM_SNAP-IN_POT

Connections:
+12V: C2.1, C4.1, C16.1, C18.1, C20.1, C22.1, C24.+, D1.C, IC1.11, IC2.4, IC4.8, IC5.4, R2.2, R11.2, R18.1, R25.2, R34.2, R41.1, R54.2, U1.8, U2.8
-12V: C3.2, C5.2, C17.2, C19.2, C21.2, C23.2, C25.-, D2.A, IC1.6, IC2.11, IC4.4, IC5.11, R9.1, R18.3, R23.1, R32.1, R41.3, R46.1, U1.4, U2.4
CHANNEL_A: R21.1, SJ1.2, U$4.P$1_TIP
CHANNEL_A_OUT: R50.1, SJ1.1, U$4.P$2_SWITCH
CHANNEL_B: R44.1, SJ2.2, U$8.P$1_TIP
CHANNEL_B_OUT: R51.1, SJ2.1, U$8.P$2_SWITCH
GND: C1.GND1, C1.GND2, C1.GND3, C1.GND4, C1.GND5, C1.GND6, C2.2, C3.1, C4.2, C5.1, C16.2, C17.1, C18.2, C19.1, C20.2, C21.1, C22.2, C23.1, C24.-, C25.+, IC2.3, IC2.10, IC2.12, IC4.3, IC4.5, IC5.3, IC5.10, IC5.12, R14.1, R16.1, R20.2, R37.1, R39.1, R43.2, R55.1, T2.3, T2.5, T3.E, T5.3, T5.5, T6.E, U$1.P$3_SLEEVE, U$2.P$3_SLEEVE, U$3.P$3_SLEEVE, U$4.P$3_SLEEVE, U$6.P$3_SLEEVE, U$7.P$3_SLEEVE, U$8.P$3_SLEEVE, U$9.P$3_SLEEVE, VR1.1, VR3.1
unnamed: IC2.5, R1.2, R2.1
unnamed: C8.2, IC2.9, R3.2, R10.1
unnamed: IC2.6, IC2.7, R3.1, R4.1, R8.1
unnamed: R1.1, U$1.P$1_TIP
unnamed: C8.1, IC2.8, R10.2, T2.2
unnamed: C9.2, IC2.13, R11.1, T2.6
unnamed: R6.2, R8.2, R9.2, VR2.3
unnamed: R7.2, T1.E
unnamed: D3.A, IC2.1, R5.2, R6.1, T1.B, T1.C
unnamed: C10.2, IC1.4, R15.1, R16.2, R17.2
unnamed: D3.C, IC2.2, R4.2, R5.1, R7.1
unnamed: R12.2, T2.1, T2.4
unnamed: C9.1, IC2.14, R12.1, VR2.1
unnamed: R13.1, U$3.P$1_TIP
unnamed: IC1.3, R13.2, R14.2
unnamed: R47.1, U$9.P$1_TIP
unnamed: C10.1, IC1.5, R15.2, VR1.3
unnamed: R17.1, R18.2
unnamed: U1.5, VR1.2
unnamed: C11.2, R19.2, R20.1, U1.6
unnamed: IC5.5, R24.2, R25.1
unnamed: C11.1, R19.1, R21.2, U1.7
unnamed: T3.B, U1.1, U1.2
unnamed: U1.3, VR2.2
unnamed: IC1.1, R22.2
unnamed: R22.1, R23.2, T3.C
unnamed: C12.2, IC5.9, R26.2, R33.1
unnamed: IC5.6, IC5.7, R26.1, R27.1, R31.1
unnamed: R24.1, U$6.P$1_TIP
unnamed: R29.2, R31.2, R32.2, VR4.3
unnamed: R30.2, T4.E
unnamed: D4.A, IC5.1, R28.2, R29.1, T4.B, T4.C
unnamed: D4.C, IC5.2, R27.2, R28.1, R30.1
unnamed: C12.1, IC5.8, R33.2, T5.2
unnamed: R35.2, T5.1, T5.4
unnamed: C13.2, IC5.13, R34.1, T5.6
unnamed: C13.1, IC5.14, R35.1, VR4.1
unnamed: R36.1, U$7.P$1_TIP
unnamed: IC1.14, R36.2, R37.2
unnamed: C14.2, IC1.13, R38.1, R39.2, R40.2
unnamed: C1.NEG1, C1.NEG2, D2.C
unnamed: C1.POS1, C1.POS2, D1.A
unnamed: C14.1, IC1.12, R38.2, VR3.3
unnamed: R40.1, R41.2
unnamed: C15.2, R42.2, R43.1, U2.6
unnamed: U2.5, VR3.2
unnamed: C15.1, R42.1, R44.2, U2.7
unnamed: IC4.6, R48.1, R49.2
unnamed: T6.B, U2.1, U2.2
unnamed: U2.3, VR4.2
unnamed: IC1.16, R45.2
unnamed: R45.1, R46.2, T6.C
unnamed: IC4.1, R49.1, R52.2
unnamed: IC4.7, R47.2, R48.2
unnamed: IC4.2, R50.2, R51.2, R52.1, R53.2
unnamed: SJ3.2, U$1.P$2_SWITCH
unnamed: R53.1, U$2.P$1_TIP
unnamed: SJ4.2, U$6.P$2_SWITCH
REF_10: R54.1, R55.2, SJ3.1, SJ4.1

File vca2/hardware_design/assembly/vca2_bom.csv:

"Comment","Designator","Footprint","LCSC Part #","LCSC Part Type"
"","SJ1, SJ2, SJ3, SJ4","SJ","",""
"100k","VR1, VR2, VR3, VR4","9MM_SNAP-IN_POT","",""
"100k","R4, R5, R13, R19, R27, R28, R36, R42, R48, R49, R50, R51, R52, R53","0402_R","",""
"100k","R18, R41","RTRIM64W","",""
"100nF","C2, C3, C4, C5, C16, C17, C18, C19, C20, C21, C22, C23","0402_C","",""
"100pF","C8, C9, C12, C13","0402_C","",""
"10M","R11, R34","0402_R","",""
"10k","R10, R33, R54","0402_R","",""
"10uF","C24, C25","A/3216-18W","",""
"15k","R22, R45","0402_R","",""
"1M","R2, R3, R17, R25, R26, R40","0402_R","",""
"1N4148","D3, D4","SOD-123","",""
"1k","R1, R21, R24, R44, R47","0402_R","",""
"1k5","R12, R35","0402_R","",""
"220R","R6, R7, R29, R30","0402_R","",""
"22pF","C10, C11, C14, C15","0402_C","",""
"2N3906","T1, T3, T4, T6","SOT23-BEC","",""
"33k","R9, R32","0402_R","",""
"47k","R15, R38","0402_R","",""
"50k","R55","0402_R","",""
"56k","R8, R31","0402_R","",""
"680R","R14, R16, R37, R39","0402_R","",""
"680k","R23, R46","0402_R","",""
"68k","R20, R43","0402_R","",""
"BC847BS","T2, T5","SOT363","",""
"EURO_POWER_LOCKFAT-LOCK","C1","EURO_PWR_HEADER_LOCK","",""
"FIDUCIAL1X2","FD1, FD2, FD3, FD4","FIDUCIAL-1X2","",""
"LM13700M","IC1","SO16","",""
"NCS20074D","IC2, IC5","SOIC-14_150MIL","",""
"OSHW-LOGOM","LOGO1","OSHW-LOGO-M","",""
"STTH102A","D1, D2","SMADIODE","",""
"TL072CD","IC4, U1, U2","SOIC8","",""
"WQP-PJ301M-12_JACK","U$1, U$2, U$3, U$4, U$6, U$7, U$8, U$9","WQP-PJ301M-12_JACK","",""
